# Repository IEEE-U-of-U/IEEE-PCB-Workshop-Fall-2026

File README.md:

# IEEE PCB Workshop Fall 2026

## Introduction
Welcome to the IEEE PCB Workshop Series for Fall 2026 at the University of Utah!

## General Information

We will be hosting this workshop over 6-7 weeks this semester, currently scheduled for **Tuesdays at 4:00 PM to 5:30 PM** beginning September 15th. Sessions may go overtime to 6:00 PM depending on the topic covered. To help alleviate these longer sessions, food may be provided (tentatively planned). All planned dates are shown below.

The workshops will be held in **WEB L102** unless otherwise specified.

We will be presenting a design for a *NFC Luggage Tag* and all participants are invited to participate in designing, manufacturing, and assembling their own PCBs, which they will be able to keep at the end.

__Workshop Goals__

- Introduction to PCB design
- Introduction to ECAD software (Altium, KiCAD)
- Introduction to Schematic Layout
- Introduction to PCB Layout
- Basics of PCB Manufacturing
- Introduction to Soldering
- Introduction to Verification and Debugging

## ECAD Software

### ALTIUM Designer (Highly Recommended)
Altium is the software that is going to be desmonstrated during the workshop and will be the easiest to follow along. All resources provided will be natively supported in Altium Designer.

If you plan to use Altium, please complete the instructions for registering and installing Altium on a personal machine. This allows us to immediately begin our workshop sessions without troubleshooting.

Altium License Instructions:
https://docs.google.com/document/d/1AU2HPewD7sdPoBuVvdMO27dwBopvW5h48ppQYsgPDJ0/edit?usp=sharing

### KiCAD

Please install KiCAD if you are not using Altium. While we do support this program, as KiCAD can import Altium files, we will be focusing on Altium Designer.

KiCAD Official Page:
https://www.kicad.org/

## Schedule

| DATE   | SESSION Title | LINK |
|--------|---------------|------|
| Sept 15  | Introduction to Schematics | [Week 01](https://github.com/IEEE-U-of-U/IEEE-PCB-Workshop-Fall-2026/tree/main/Week01) |
| Sept 22 | Schematics and Components | [Week 02](https://github.com/IEEE-U-of-U/IEEE-PCB-Workshop-Fall-2026/tree/main/Week02) |
| Sept 29 | Introduction to PCB Layout | [Week 03](https://github.com/IEEE-U-of-U/IEEE-PCB-Workshop-Fall-2026/tree/main/Week03) |
| Oct 6 | Footprints and PCB Layout | [Week 04](https://github.com/IEEE-U-of-U/IEEE-PCB-Workshop-Fall-2026/tree/main/Week04) |
| TBD | Soldering Week 1 | [Week 05](https://github.com/IEEE-U-of-U/IEEE-PCB-Workshop-Fall-2026/tree/main/Week05) |
| TBD | Soldering Week 2 | [Week 06](https://github.com/IEEE-U-of-U/IEEE-PCB-Workshop-Fall-2026/tree/main/Week06) |
| TBD | Soldering Week 3 | [Week 07](https://github.com/IEEE-U-of-U/IEEE-PCB-Workshop-Fall-2026/tree/main/Week07) |

While it is recommended to attend all sessions, we will provide the design and workshop files through a GitHub repository. To stay up to date, please be sure to follow along to not fall behind.

## Contact Info

- Questions may be routed to the IEEE email: ieee.studentbranch.uofu@gmail.com

## Sign-Up Flyer

Sign-Up Form:
[Form](https://forms.gle/LWkrtqE1gXzcFd4B7)

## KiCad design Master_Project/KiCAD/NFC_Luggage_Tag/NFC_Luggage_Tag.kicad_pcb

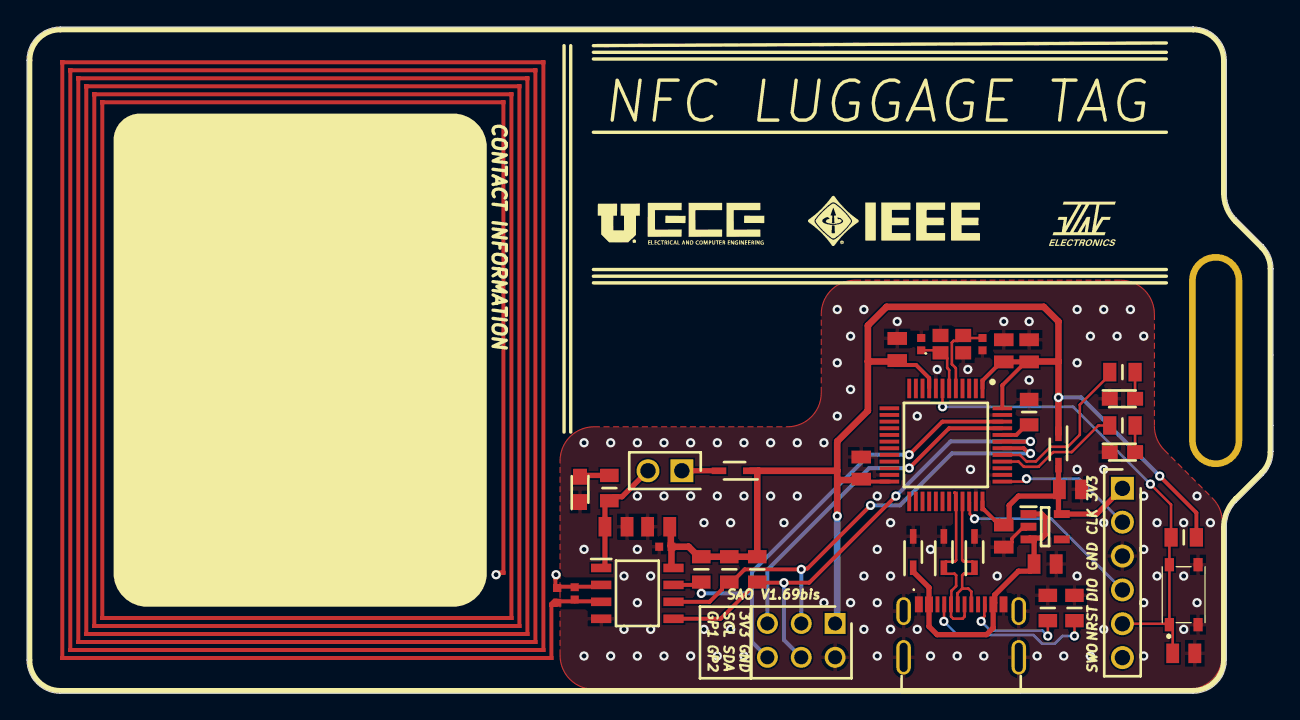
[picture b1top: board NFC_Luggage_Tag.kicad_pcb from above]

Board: 2 copper layers, 93.5 x 50.0 mm, 42 parts (0 on the bottom side), 27 nets.

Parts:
A1: Antenna; NFC Antenna 45 x 37
C1, C3, C5, C6, C7, C8, C9, C10, C11, C12: 100n; CAP0805
C2, C4, C13, C14: 10p; CAP0402
D1, D2, D3: LED; LEDM2012X80N
D4, D5, D6: 5V; SOD323
D7, D8: 1N5819; SOD323
H1: Header; HEADER_2X3
H2: Header; Header_1X6
H3: Header; Header_1X2
IC1: ST25DV16KC-IE6S3; SOIC8
IC2: STM32L052C8T6; QFP50P900X900X160-48N
J1: USB C; USB TYPE C 12 PIN
R1, R8, R9: 5.11k; RESC0805
R2, R3, R4, R5, R6, R7, R10: 10k; RESC0805
SW1: Tactile Switch - 1; Tactile Button 4.2mm x 3.2mm
U1: TPS7A0333PDBVR; SOT23-5
Y1: ECS-120-10-36B2-CWY-TR; ECS1201036B2CWYTR

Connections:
+3.3_USB: C9.1, C11.1, D7.2, H2.1, IC2.36, U1.5
GND: C1.2, C3.2, C4.2, C5.2, C6.2, C7.2, C8.2, C9.2, C10.2, C11.2, C12.2, C13.2, C14.1, D1.1, D2.1, D3.1, D4.2, D5.2, D6.2, H1.2, H2.3, IC1.4, IC2.8, IC2.23, IC2.35, IC2.38, IC2.47, J1.1, J1.2, J1.3, J1.14, J1.15, J1.16, R7.2, R8.1, R9.1, SW1.3, SW1.4, U1.2, Y1.2, Y1.4
I2C1_SCL: H1.3, IC1.6, IC2.42, R3.2
I2C1_SDA: H1.4, IC1.5, IC2.43, R4.2
LED_INDC0: IC2.41, R5.1
LED_INDC1: IC2.40, R6.1
NFC_GPO: H1.6, IC1.7, IC2.46, R2.2
NRST: C12.1, H2.5, IC2.7, R10.1, SW1.1, SW1.2
NetA1_1: A1.1, C2.1, IC1.2
NetA1_2: A1.2, C2.2, IC1.3
NetD1_2: D1.2, R1.2
NetD2_2: D2.2, R5.2
NetD3_2: D3.2, R6.2
NetD8_2: D8.2, H3.1
NetH1_5: H1.5, IC2.45
NetIC2_44: IC2.44, R7.1
NetJ1_5: J1.5, R8.2
NetJ1_11: J1.11, R9.2
SYS_SWCLK: H2.2, IC2.37
SYS_SWDIO: H2.4, IC2.34
USB_D_N: D5.1, IC2.32, J1.8, J1.10
USB_D_P: D6.1, IC2.33, J1.7, J1.9
V_EH: C1.1, H3.2, IC1.1, R1.1
V_MCU: C3.1, C4.1, C5.1, C6.1, C7.1, C8.1, D7.1, D8.1, H1.1, IC1.8, IC2.1, IC2.9, IC2.24, IC2.48, R2.1, R3.1, R4.1, R10.2
V_USB: C10.1, D4.1, J1.4, J1.13, U1.1, U1.3
XIN: C13.1, IC2.5, Y1.3
XOUT: C14.2, IC2.6, Y1.1
